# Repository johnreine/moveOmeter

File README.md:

# moveOmeter

### Privacy-Preserving IoT Monitoring for Elderly Care

> Help your loved ones live independently longer with non-invasive, radar-based health monitoring.

---

## 🎯 The Problem

Families want to care for aging loved ones while respecting their independence and privacy. Traditional monitoring requires cameras (invasive) or wearables (forgotten/rejected).

## 💡 Our Solution

**moveOmeter** uses mmWave radar technology to monitor health and activity patterns without cameras or wearables. The system tracks:

- 🚶 **Activity & Movement** - Daily patterns and mobility changes
- 😴 **Sleep Quality** - Duration, disturbances, and sleep score
- ❤️ **Vital Signs** - Heart rate and respiration (contactless)
- 🚨 **Fall Detection** - Instant alerts for falls or emergencies
- 🏠 **Presence Detection** - Know when they're home or away

**No cameras. No wearables. No user interaction required.**

---

## ✨ Key Features

### Privacy-First Design
- ✅ Radar technology (sees motion, not images)
- ✅ No video, no photos, no recording
- ✅ HIPAA-compliant architecture ready

### Real-Time Monitoring
- ✅ Live web dashboard with charts
- ✅ Mobile-responsive interface
- ✅ Instant WebSocket updates
- ✅ Historical trend analysis

### Smart & Adaptive
- ✅ Learns individual patterns
- ✅ Detects anomalies automatically
- ✅ Over-the-air firmware updates
- ✅ Remote configuration

### Secure & Scalable
- ✅ Role-based access control (admin/employee/caretaker/resident)
- ✅ End-to-end encryption
- ✅ Audit logging
- ✅ Designed to scale to millions of users

---

## 📸 Screenshots

### Real-Time Dashboard
> 🚧 *Screenshot coming soon - see [deployment guide](./deployment/QUICKSTART.md) to run locally*

**Features visible in dashboard:**
- Live timeline charts (1-hour, 12-hour, 24-hour views)
- Activity metrics (movement, presence, sleep quality)
- Device status (online/offline)
- Manual annotations
- Alert notifications

### Admin Panel
> 🚧 *Screenshot coming soon*

**Manage users and devices:**
- User management (create, edit, roles)
- Device assignment
- Access control
- Audit logs

---

## 🚀 Quick Start

### Prerequisites
- ESP32-C6 Feather development board
- DFRobot SEN0623 mmWave sensor
- Supabase account (free tier works)
- Arduino IDE 2.x

### 5-Minute Setup

1. **Clone the repository**
   ```bash
   git clone https://github.com/johnreine/moveOmeter.git
   cd moveOmeter
   ```

2. **Set up database**
   - Create Supabase project at https://supabase.com
   - Run migrations: `database/run_all_migrations.sql`

3. **Configure firmware**
   ```bash
   # Edit pictureFrame/software/mmWave_Supabase_collector/config.h
   # Add your WiFi credentials and Supabase URL/key
   ```

4. **Upload to ESP32-C6**
   - Open Arduino IDE
   - Select board: ESP32C6 Dev Module
   - Upload sketch

5. **Start dashboard**
   ```bash
   cd web/dashboard
   python3 -m http.server 8000
   open http://localhost:8000
   ```

**Full setup guide:** [deployment/QUICKSTART.md](./deployment/QUICKSTART.md)

---

## 🏗️ Architecture

```
┌──────────────────────────────────────────────────────┐
│  ESP32-C6 + mmWave Sensor (DFRobot SEN0623)         │
│  • Collects 40+ health metrics every 20 seconds     │
│  • WiFi upload to cloud                             │
│  • OTA firmware updates                             │
└─────────────────┬────────────────────────────────────┘
                  │ HTTPS Upload
                  ▼
┌──────────────────────────────────────────────────────┐
│  Supabase Backend (PostgreSQL + Auth + Realtime)    │
│  • Time-series sensor data storage                  │
│  • Role-based access control (RLS)                  │
│  • Real-time WebSocket subscriptions                │
│  • OTA firmware distribution                        │
└─────────────────┬────────────────────────────────────┘
                  │ WebSocket + REST API
                  ▼
┌──────────────────────────────────────────────────────┐
│  Web Dashboard (Vanilla JS + Chart.js)              │
│  • Live charts and metrics                          │
│  • User authentication                              │
│  • Admin panel                                      │
│  • Mobile responsive                                │
└──────────────────────────────────────────────────────┘
```

---

## 🛠️ Tech Stack

### Hardware

### Backend

### Frontend

### Firmware

### Deployment

---

## 📚 Documentation

| Document | Description |
|----------|-------------|
| **[Project Status](./PROJECT_STATUS.md)** | Complete overview of features and progress |
| **[Development Roadmap](./ROADMAP.md)** | 6-12 month development plan |
| **[AI Agent Guide](./AI_AGENT_GUIDE.md)** | For AI coding assistants (Claude, GPT, etc.) |
| **[Quick Start](./deployment/QUICKSTART.md)** | Get running in 5 minutes |
| **[Full Deployment Guide](./deployment/README.md)** | Production deployment instructions |
| **[Authentication Setup](./web/dashboard/AUTH_SETUP.md)** | User management and security |
| **[Firmware README](./pictureFrame/software/mmWave_Supabase_collector/README.md)** | ESP32-C6 firmware details |
| **[OTA Testing Guide](./database/OTA_QUICK_TEST.md)** | Test firmware updates |

---

## 🗺️ Roadmap

### ✅ Current (v1.0) - Complete
- ESP32-C6 firmware with dual collection modes
- Real-time web dashboard with charts
- Authentication system (4 user roles)
- Admin panel for user/device management
- OTA firmware update infrastructure
- Timeline annotations
- Data aggregation for performance

### 🚧 Next Month (v1.1)
- [ ] Multi-device support in dashboard
- [ ] Progressive Web App (PWA)
- [ ] Email notifications
- [ ] Activity summary reports
- [ ] Mobile-responsive design improvements

### 🔮 Next Quarter (v1.5)
- [ ] React Native mobile app (iOS + Android)
- [ ] Predictive health alerts (ML-based)
- [ ] Medication reminder integration
- [ ] Voice integration (Alexa/Google Home)
- [ ] Family sharing features

### 🎯 Long-Term Vision
- AI-powered gait analysis and fall risk prediction
- Behavior pattern recognition
- White-label solution for senior living facilities
- Integration ecosystem (Apple Health, etc.)

**Full roadmap:** [ROADMAP.md](./ROADMAP.md)

---

## 🤝 Contributing

We welcome contributions! This project is currently in active development.

### How to Contribute

1. **Read the docs**
   - [Project Status](./PROJECT_STATUS.md) - Current state
   - [Roadmap](./ROADMAP.md) - Planned features
   - [AI Agent Guide](./AI_AGENT_GUIDE.md) - Technical details

2. **Find an issue**
   - Check [Issues](https://github.com/johnreine/moveOmeter/issues) for open tasks
   - Look for `good first issue` or `help wanted` labels

3. **Fork and create a branch**
   ```bash
   git checkout -b feature/your-feature-name
   ```

4. **Make your changes**
   - Follow existing code style
   - Add tests if applicable
   - Update documentation

5. **Submit a pull request**
   - Clear description of changes
   - Reference related issues
   - Screenshots for UI changes

### Development Setup

```bash
# Clone repository
git clone https://github.com/johnreine/moveOmeter.git
cd moveOmeter

# Install Arduino libraries
# - ESPSupabase (by jhagas)
# - DFRobot_HumanDetection (by DFRobot)

# Set up Supabase
# 1. Create account at https://supabase.com
# 2. Run database/run_all_migrations.sql

# Start local dashboard
cd web/dashboard
python3 -m http.server 8000
```

### Code Style

- **JavaScript:** ES6+, async/await, template literals
- **C++:** Arduino style, comments for complex logic
- **SQL:** Uppercase keywords, clear comments
- **Documentation:** Markdown with clear headings

---

## 🌟 Use Cases

### For Families
- Monitor aging parents remotely
- Peace of mind while at work
- Early detection of health changes
- Respect privacy (no cameras)

### For Caregivers
- Track multiple clients
- Shift handoff notes
- Medication reminders
- Fall alerts

### For Senior Living Facilities
- Monitor all residents
- Staff coordination
- Compliance reporting
- Emergency response

### For Healthcare Providers
- Remote patient monitoring
- Post-discharge tracking
- Chronic condition management
- Reduce hospital readmissions

---

## 📊 Project Stats

- **40 files** of comprehensive documentation
- **16,000+ lines** of code and docs
- **40+ sensor metrics** collected
- **4 user roles** with granular permissions
- **3 timeline views** (1h, 12h, 24h)
- **97% bandwidth reduction** with smart keep-alive
- **OTA updates** for remote firmware deployment

---

## 🔐 Security & Privacy

### Privacy Protections
- ✅ No cameras or video recording
- ✅ Radar technology (motion only, not images)
- ✅ Data encrypted in transit (HTTPS)
- ✅ Data encrypted at rest (Supabase)
- ✅ Row Level Security (RLS) for data isolation

### Compliance Ready
- 🔜 HIPAA compliance architecture
- 🔜 GDPR data handling
- 🔜 SOC 2 Type II準備中

### Security Features
- Multi-factor authentication (MFA) support
- Passkey/WebAuthn ready
- Audit logging for all actions
- Role-based access control
- Automatic session management

---

## 🛡️ Testing

### Current Test Coverage
- ✅ End-to-end firmware testing
- ✅ Real-time data pipeline
- ✅ Authentication flows
- ✅ Role-based access control
- 🚧 Cross-browser compatibility
- 🚧 Scale testing (100-1000 devices)

### Tested Environments
- **Firmware:** ESP32-C6 Feather
- **Browsers:** Chrome, Firefox, Safari (desktop)
- **Database:** Supabase (PostgreSQL 15)
- **Deployment:** Ubuntu 22.04 + Nginx

---

## 💰 Cost to Run

### Development (Current)
- **Supabase:** Free tier (good for 10 devices)
- **Digital Ocean:** $10-20/month
- **Total:** ~$10-20/month

### Small Deployment (100 devices)
- **Supabase:** $25/month (Pro tier)
- **Digital Ocean:** $20/month
- **Total:** ~$45/month

### Medium Scale (1,000 devices)
- **Supabase:** $599/month (Team tier)
- **Digital Ocean/AWS:** $100-200/month
- **Total:** ~$700-800/month

**Note:** Costs scale linearly. See [ROADMAP.md](./ROADMAP.md) for scaling details.

---

## 📄 License

**Proprietary** - All rights reserved.

This project is currently not open source. Contact for licensing inquiries.

---

## 📞 Contact & Support

### Questions or Issues?
1. Check [Project Status](./PROJECT_STATUS.md) and [Roadmap](./ROADMAP.md)
2. Review [documentation](./deployment/README.md)
3. Open an [Issue](https://github.com/johnreine/moveOmeter/issues)

### Business Inquiries
- **Email:** contact@moveometer.com (TBD)
- **Website:** https://moveometer.com (TBD)

### For Contributors
- Join discussions in [Issues](https://github.com/johnreine/moveOmeter/issues)
- Submit [Pull Requests](https://github.com/johnreine/moveOmeter/pulls)
- See [AI Agent Guide](./AI_AGENT_GUIDE.md) for technical details

---

## 🙏 Acknowledgments

### Hardware
- **Adafruit** - ESP32-C6 Feather development board
- **DFRobot** - SEN0623 mmWave sensor

### Software & Services
- **Supabase** - Backend-as-a-Service platform
- **Chart.js** - Beautiful data visualization
- **Arduino** - ESP32 development framework

### Inspiration
Built with care for families supporting elderly loved ones. Inspired by the need for privacy-preserving health monitoring that maintains dignity and independence.

---

## ⭐ Star History

If you find this project useful, consider giving it a star! ⭐

---

## 📈 Project Activity

---

<div align="center">

**Made with ❤️ for better elderly care**

[Documentation](./PROJECT_STATUS.md) • [Roadmap](./ROADMAP.md) • [Contributing](#contributing) • [License](#license)

</div>

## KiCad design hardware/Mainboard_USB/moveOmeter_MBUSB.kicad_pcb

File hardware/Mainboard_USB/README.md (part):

# moveOmeter Mainboard-USB (rev A, 4 layers, routed 11/13)

A passive backboard for two SB1 rev B sensor boards. It powers both from one USB-C port and brings every sensor
signal out to headers, so a PC can run all four radars and both I2C buses through plug-in USB adapters. The mic
headers need an external I2S master (the mics are clock slaves; nothing on this board drives BCLK / WS). It has no processor. It has the same size, mounting and FFC positions the ESP32-S3 Mainboard will use, so
the enclosure and 3D-printed bracket can be tried out now. Generated 2026-10-31 from `tools/` (same generator as SB1).

## How it fits

- The board stands upright behind the SB1 V, parallel to the wall. The V stands 35 mm out, its point toward the
  room, apex at X 50. Its footprint on the front is X 20.3-79.7, y 8-84 (dashed outline on F.Fab).
- **SB1-A** (left) plugs into **J2**, **SB1-B** (right) into **J3**, each from its SB1's only ZIF, J7 (one ZIF per SB1
  since 11/8). Both are Molex 200528-0200 ZIFs (20-way, 1.0 mm, ear-tab lock), standing on end **inside the V**,
  centred on y 50.5, the same height as SB1's ZIF, **both opening toward -X**: J2's mouth at X 38.9 (turned round on
  11/8; it used to open toward the centre at X 33.0), J3's at X 67.0. **Both are wired in reverse (pad n = wire 21 - n,
  GND on pad 20)**, to match SB1's J7, so GND (wire 1) is at the bottom of both and the two links are identical.
  Cable: 20-way 1.00 mm, same-side contacts (Type A), ~51 mm, the same for both sides; never Type D. SB1-B's cable
  leaves its SB1 toward the apex, U-turns inside the V and comes into J3 from the centre; SB1-A's runs out along its SB1
  back, swings round 135 degrees and comes into J2 from the left. Full workup and drawings (pins, cable faces, X / Y
  dimensions): SB1's README, FFC link, and `docs/ffc_top_view.png`, `docs/ffc_links_flat.png`.
- The front strips where each cable runs close to the board (X 27-38.9 left of J2, X 54-67 left of J3, y 36-65) are kept
  free of parts. The bracket on H5-H8 must leave that space open too.
- **Holes:** ten M3 (3.2 mm).
  - H5-H8 at (32, 15), (68, 15), (32, 77), (68, 77), under the V (7 mm inside its top and bottom), for the bracket that holds both SB1s.
  - H1-H4 at the corners of the core (4, 4), (96, 4), (4, 86), (96, 86), and H9 / H10 at the bottom corners
    (4, 117), (96, 117), for the enclosure.
  - Keep-out 3.5 mm on both sides.

## Board (100 x 121 mm, 2 layers)

The size comes from the design: 100 mm wide for the V plus the two ZIFs. The core (y 0-90) sits behind the V; the
wing below it (y 90-121) carries the four USB-serial sticks. (150 mm until SB1 shrank by 10 mm on 10/31, 140 mm until
the sticks plugged straight in on 11/01.)

- **Front, lower left:** USB-C J1 (GCT USB4125, power only) at the left edge, mouth out. 5.1k CC pull-downs (R1, R2),
  SMBJ5.0A TVS (D1), 470 uF polymer (C1), 10 uF + 100 nF, green power LED (R3, D2).
- **Front, wing:** the bench light sensor J14, an Adafruit 4162 VEML7700 breakout (John, 10/31) in a 1x5 socket
  (Sullins PPTC051LFBN-RC), centred below the V so the SB1s don't shade it. Socket row at y 88.5; the breakout hangs
  down over the back UART headers' pin stubs (it sits ~11 mm up), sensor at about y 100. On I2C-A at 0x10, powered from
  the I2C-A adapter's 3.3 V (its own pull-ups go to that). Pins 1 VIN, 2 3Vo (not used), 3 GND, 4 SCL, 5 SDA. SB1's
  own VEML7700 footprint is DNP so the two don't clash at 0x10.
- **Back, core:**
  - I2C-A / I2C-B headers (J8, J9) at the top corners, each above a parking pad for an MCP2221A USB-I2C breakout.
    4.7k pull-up footprints to the adapter's 3.3 V (R4-R7, DNP: SB1 has its own pull-ups).
  - Mic headers (J10, J11) and status headers (J12, J13: P20, spare 1, spare 2, GND) below the MCP2221A pads at the
    sides (y 52 / 60; moved 11/4 from the middle, where their pins came through under the new ZIF positions).
- **Back, wing:** four right-angle 1x5 female sockets (J4-J7, Sullins PPTC051LGBN-RC) with the pin row at y 94. John's
  CP2102 sticks (USB-A plug, right-angle pins 3V3 / TXD / RXD / GND / +5V) plug straight in **chip side down**: resting
  on their header plastic puts their pins at the socket's height, and chip side down is the way round that lands 3V3
  on pin 1. Each stick lies flat with its USB plug hanging past the bottom edge, to plug into a hub or a USB-A extension
  lead. Its outline is on the back silk, and "CP2102 CHIP SIDE DOWN" inside it. Plugged in chip side up, its TXD would
  land on the GND pin. A 1k resistor (R8-R11)
  above each header sits in series with the adapter's TXD.
- Back silk labels read as seen from behind; pin 1 is the square pad.
- **Stackup (4 layers since 11/13):** JLC04161H-7628, 1.6 mm, as SB1 / TB1: F.Cu signals + GND pour / In1 GND plane / In2 +5V plane / B.Cu signals + GND pour. (2 layers until 11/13; four Freerouting runs never finished.)
- **Net classes (11/6):** Default 0.2 mm track, 0.175 mm clearance (as on SB1: a 0.2 mm track fits between the 1 mm-pitch ZIF pads), 0.6 / 0.3 vias; Power (+5V) 1.0 mm track, 0.2 mm clearance, 0.8 / 0.4 vias, since +5V carries both SB1s (~1.5 A peak). Neck +5V down to 0.3-0.4 mm for the last mm into the ZIF pads (pins 2-3); hole clearance 0.175 mm.
- **Checks (all pass):** courtyards, pins under the other side's parts, hole keep-outs, FFC bands free, nothing taller
  than 12 mm under the V, back parts off the MCP2221A parking pads and the stick outlines, edges (J1 is meant to be at the edge), and every
  netlist pin has its pad and net.

## Headers

| Ref | For | Pins (1 to n) |
| --- | --- | --- |
| J4 / J7 | LD6004 A / B UART (115200 default; 460800 on the bench modules since 10/14) | 3V3 (nc), TXD, RXD, GND, 5V (nc) |
| J5 / J6 | LD2450 A / B UART (256000) | 3V3 (nc), TXD, RXD, GND, 5V (nc) |
| J8 / J9 | I2C A / B | GND, 3V3, SDA, SCL |
| J14 | VEML7700 breakout (on I2C-A) | VIN, 3Vo (nc), GND, SCL, SDA |
| J10 / J11 | Mics A / B | BCLK, WS, DATA, GND |
| J12 / J13 | Status A / B | P20, spare 1, spare 2, GND |

The UART sockets take John's CP2102 sticks (Amazon B0FJRTL572, 3V3 / TXD / RXD / GND / +5V): the stick's TXD drives
the radar's RX (through the 1k) and its RXD reads the radar's TX. The sticks' 3V3 and 5V pins aren't connected, so they
don't back-feed the sensors. The stick outline (16 x 21 mm PCB) comes from sellers' listings (14-15 mm wide, 41-45 mm
with the plug, ~21 mm PCB): check it against one in hand, and check that its USB plug clears the board edge chip side
down. The MCP2221A parking pads (about 18 x 27 mm) are still placeholders until that breakout is chosen. The sockets'
3D model orientation hasn't been checked in KiCad's 3D viewer yet.

**Resetting the radars:** each adapter's TXD idles high. Without a series resistor it could hold an unpowered radar
partly up through its RX input clamp, so unplugging J1 wouldn't be a clean power-cycle. A 1k in series with each
adapter TXD (R8-R11, John 10/31) limits that current to under ~3 mA, so unplugging J1 is a reset. The 1k plus SB1's
100 ohm is far too small to matter at 256000 baud.

## Ordering

`bom_board.csv`: about $14.40 a board at qty-1 prices, including the VEML7700 breakout and its socket, not counting
the USB adapters or the FFCs.

## 3D models

KiCad's library has models for the standard parts. The rest are in `3dmodels/`, written by `tools/layout/mk3d.py` (run
by `tools/rebuild.sh`) and referenced as `${KIPRJMOD}/3dmodels/...` in the footprints. They are VRML files, so KiCad's
3D viewer shows them, but a STEP export of the board leaves them out.
- `MBUSB_Adafruit_4162_VEML7700_on_socket.wrl` (J14): Adafruit has no 3D file for the 4162 (only for the right-angle
  5378), so this one is built from their board file: outline, holes, sensor, regulator and STEMMA QT sockets. It sits
  on its header in the 1x5 socket, top at 12.6 mm.
- `Molex_200528-0200_approx.wrl` (J2, J3): a simplified housing, actuator and contacts.
- `3dmodels/vendor/Adafruit_4471_MCP2221A_Breakout.step`: Adafruit's STEP of the MCP2221A breakout, for enclosure
  CAD. It isn't a footprint on the board.
- Mounting holes and solder jumpers have no model, as in KiCad's own library.
- The Molex 200528-0200 footprint points to an official STEP file that this KiCad install doesn't have. The board uses
  the approximate model instead (`MODEL_OVERRIDE` in the board script).

## Regenerating

`sh tools/rebuild.sh` writes the schematic, library, netlist report and BOM (`tools/build.py`), the placement and
silk pads / slots / labels (`tools/layout/place_mbusb.py`), the breakout footprint (`mkfp_mbusb.py`), the board (`mkpcb_mbusb.py`), runs the rule check
(`verify_mbusb.py`) and draws `docs/MBUSB_board.png`. `tools/layout/mkpro_mbusb.py` wrote the project file once
from SB1's. Parts and nets are in `tools/design.py`.

Once you edit in KiCad, KiCad is the source of truth.

## Silkscreen labels (11/6)

`tools/layout/silkrefs.py` (run by `rebuild.sh` after the board is written) moves every reference designator beside its own part so the board can be debugged with everything fitted: never under a part body, off pads, other silk and other labels, 0.5 mm inside the edge. Text is 0.8 mm (0.12 stroke), dropping to 0.7 / 0.6 mm only where there's no room (on SB1 only C11, at 0.6 mm). The module pin labels under the LD6004 / LD2450 and the CP2102 notes stay where their footprints put them. If you move a part in KiCad, move its label by hand: once routing starts, KiCad owns the board.

## Mounting holes: screw keep-outs (11/6)

All ten M3 holes are unplated. Rule areas ban tracks and vias within 3.45 mm of each hole centre on both sides (bracket
screw heads on the front at H5-H8, feet / nuts on the back); GND pour is allowed there.

## Routing prep (11/13)

`tools/layout/fanout_mbusb.py` (run by `rebuild.sh` right after the board is written) applies SB1's routing lessons:
- **Edge strips:** a 0.4 mm no-track / no-via rule area inside each edge on both layers. Freerouting ignores KiCad's
  0.5 mm copper-to-edge rule; the strips put it in the DSN. Pads and pour are allowed there.
- **GND fan-out:** 18 locked GND vias, one per SMD GND pad, each on a 0.3 mm stub: the ZIF GND pads (6, 9, 11, 14, 17,
  20) on the housing side at x 41.3 (J2) / 69.43 (J3), and C2, C3, D1, D2, R1, R2. They keep the two pours joined
  however the tracks cut them up.
- **+5V into the ZIFs:** pads 18 and 19 joined at 0.4 mm, out 0.4 mm past the courtyard, then 1.0 mm for 1.1 mm, so
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
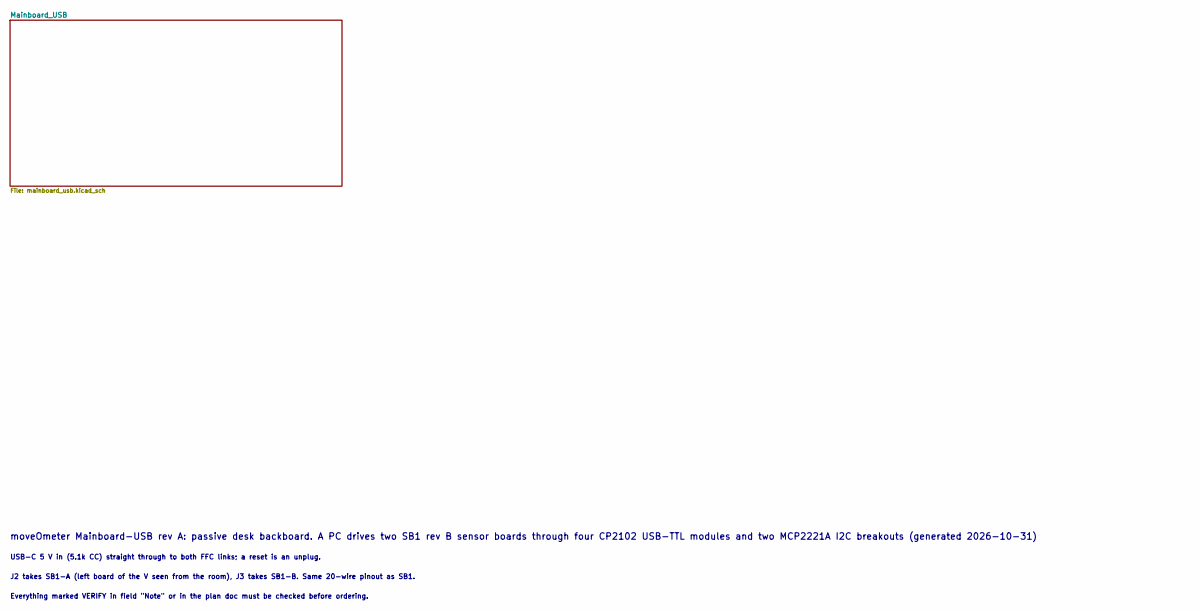
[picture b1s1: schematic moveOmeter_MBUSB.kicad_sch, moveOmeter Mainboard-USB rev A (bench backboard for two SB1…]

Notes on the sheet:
moveOmeter Mainboard-USB rev A: passive desk backboard. A PC drives two SB1 rev B sensor boards through four CP2102 USB-TTL modules and two MCP2221A I2C breakouts (generated 2026-10-31)
USB-C 5 V in (5.1k CC) straight through to both FFC links; a reset is an unplug.
J2 takes SB1-A (left board of the V seen from the room), J3 takes SB1-B. Same 20-wire pinout as SB1.
Everything marked VERIFY in field "Note" or in the plan doc must be checked before ordering.

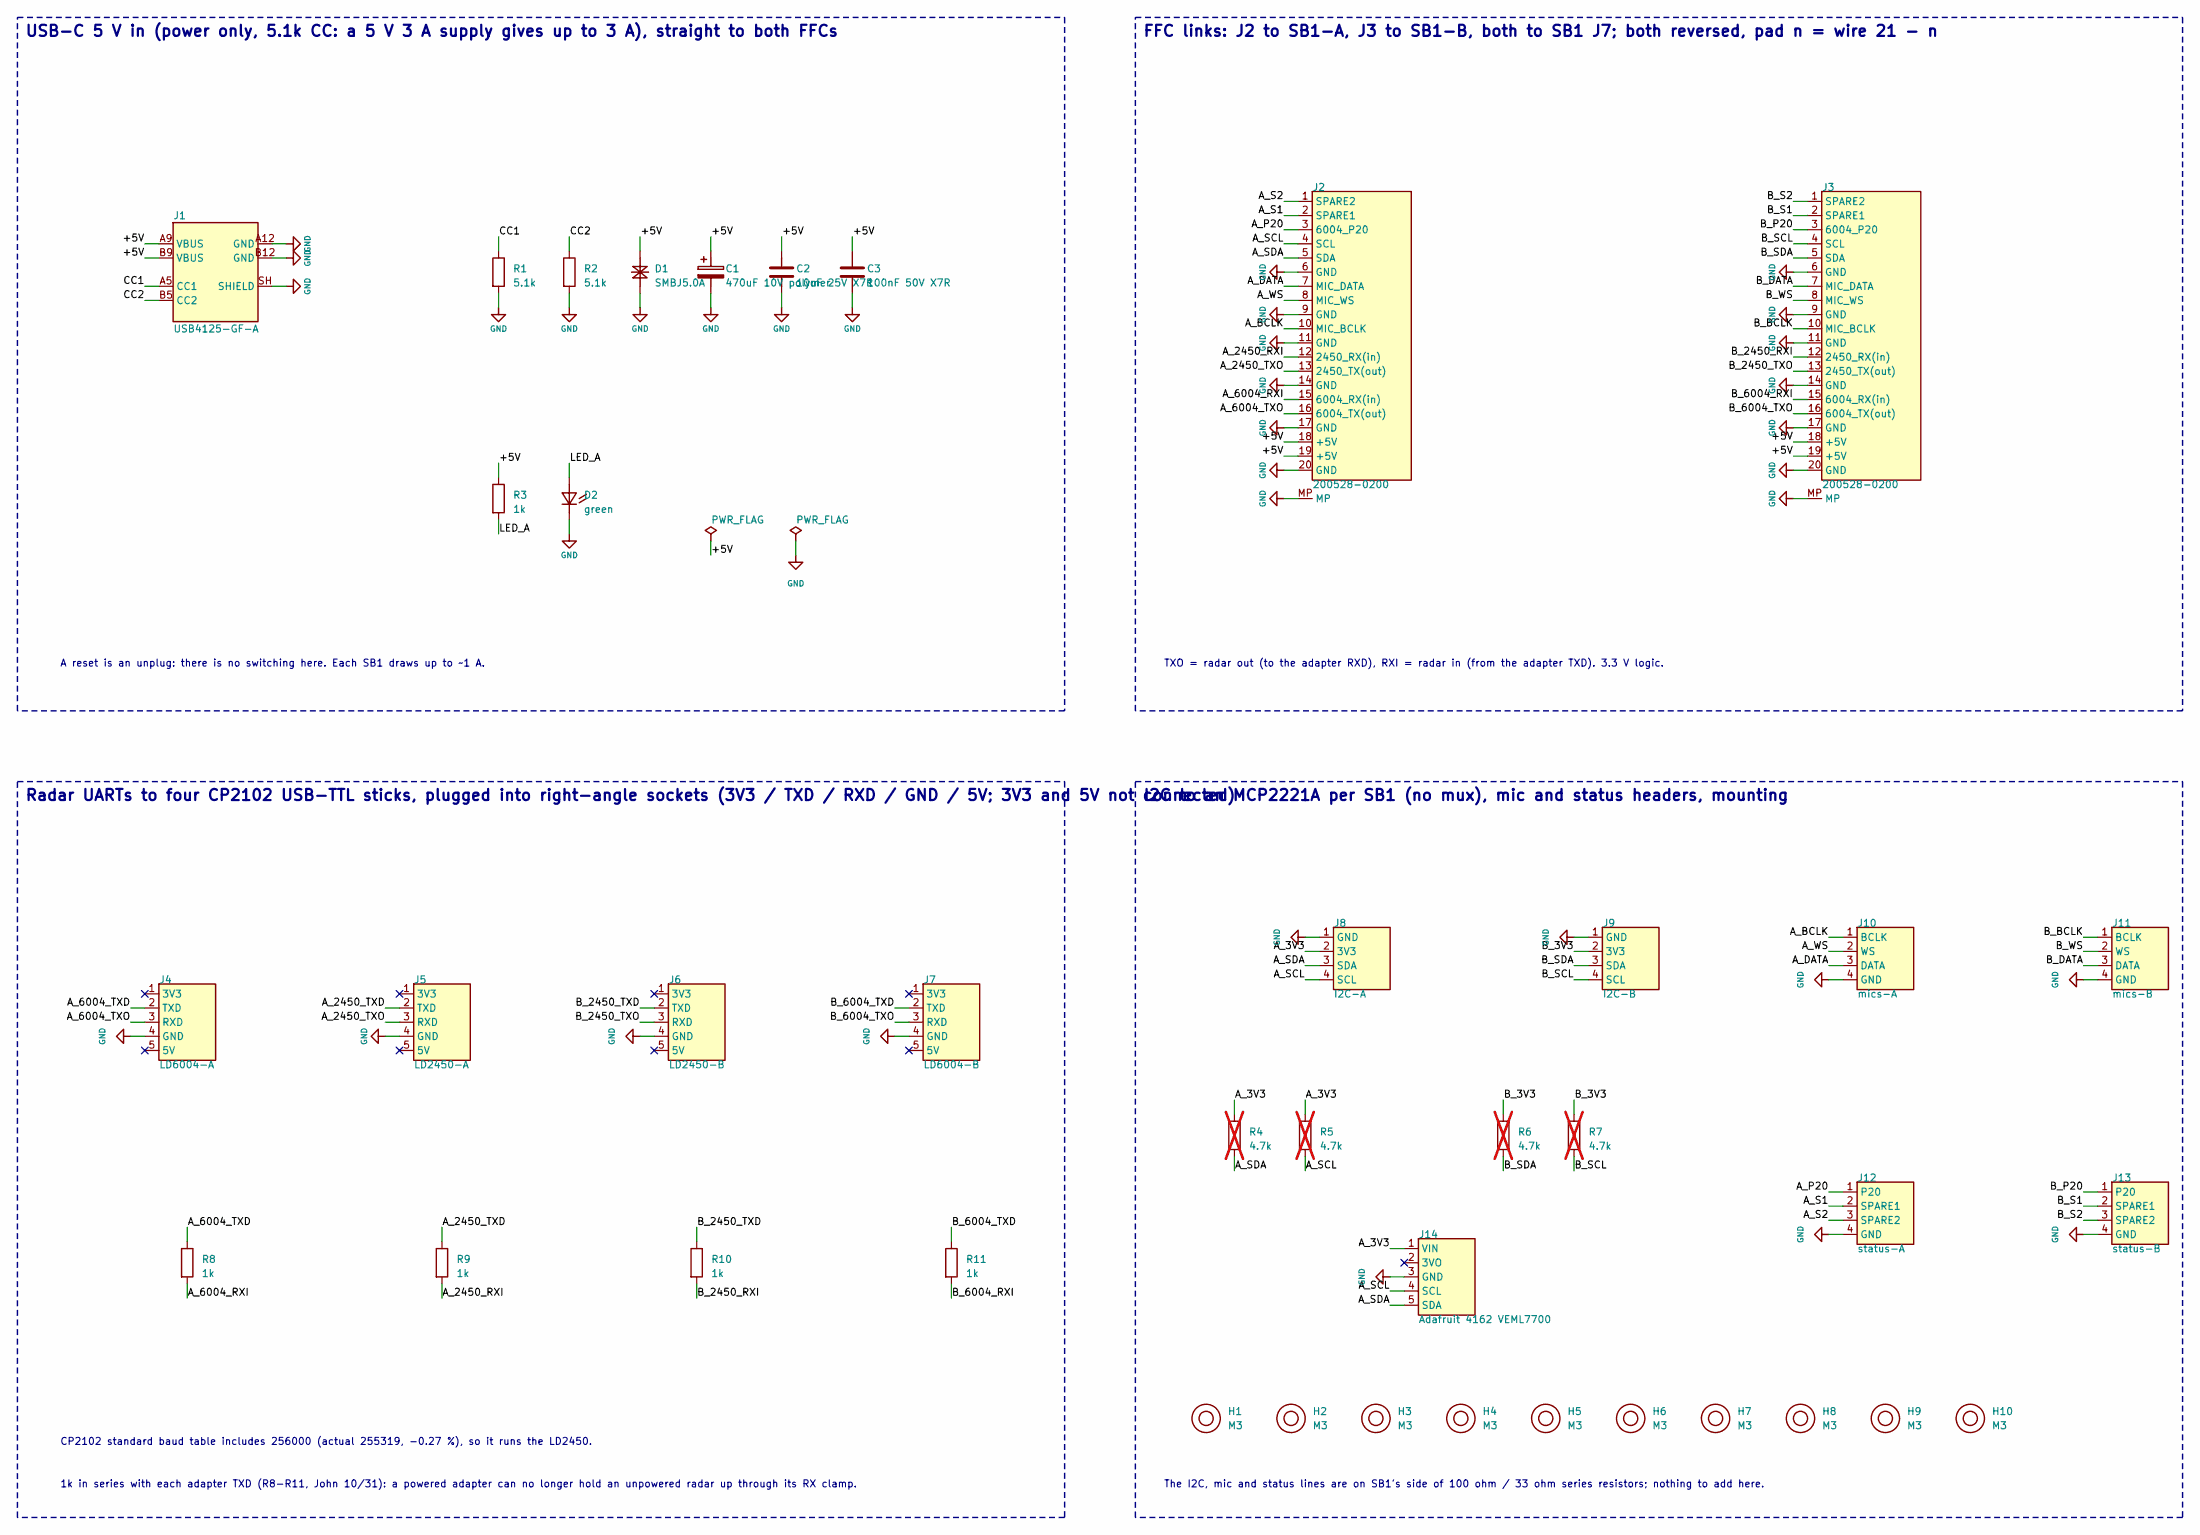
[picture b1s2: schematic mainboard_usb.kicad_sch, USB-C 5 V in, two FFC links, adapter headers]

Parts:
C1: 470uF 10V polymer; CP_Radial_D8.0mm_P3.50mm; MPN A759KS477M1AAAE014
C2: 10uF 25V X7R; C_1210_3225Metric_Pad1.33x2.70mm_HandSolder; MPN GRM32DR71E106KA12L
C3: 100nF 50V X7R; C_1206_3216Metric_Pad1.33x1.80mm_HandSolder; MPN CL31B104KBCNNNC
D1: SMBJ5.0A; D_SMB_Handsoldering; MPN SMBJ5.0A
D2: green; LED_1206_3216Metric_Pad1.42x1.75mm_HandSolder; MPN LTST-C150GKT
H1, H2, H3, H4, H5, H6, H7, H8, H9, H10: M3; MountingHole_3.2mm_M3
J1: USB4125-GF-A; USB_C_Receptacle_GCT_USB4125-xx-x_6P_TopMnt_Horizontal; MPN USB4125-GF-A
J2, J3: 200528-0200; Molex_200528-0200_1x20-1MP_P1.00mm_Horizontal; MPN 200528-0200
J4: LD6004-A; CP2102_Stick_Socket_1x05_P2.54mm_Horizontal; MPN PPTC051LGBN-RC
J5: LD2450-A; CP2102_Stick_Socket_1x05_P2.54mm_Horizontal; MPN PPTC051LGBN-RC
J6: LD2450-B; CP2102_Stick_Socket_1x05_P2.54mm_Horizontal; MPN PPTC051LGBN-RC
J7: LD6004-B; CP2102_Stick_Socket_1x05_P2.54mm_Horizontal; MPN PPTC051LGBN-RC
J8: I2C-A; PinHeader_1x04_P2.54mm_Vertical; MPN PEC04SAAN
J9: I2C-B; PinHeader_1x04_P2.54mm_Vertical; MPN PEC04SAAN
J10: mics-A; PinHeader_1x04_P2.54mm_Vertical; MPN PEC04SAAN
J11: mics-B; PinHeader_1x04_P2.54mm_Vertical; MPN PEC04SAAN
J12: status-A; PinHeader_1x04_P2.54mm_Vertical; MPN PEC04SAAN
J13: status-B; PinHeader_1x04_P2.54mm_Vertical; MPN PEC04SAAN
J14: Adafruit 4162 VEML7700; Adafruit_VEML7700_Breakout_Socket_1x05; MPN PPTC051LFBN-RC
R1, R2: 5.1k; R_1206_3216Metric_Pad1.30x1.75mm_HandSolder; MPN RC1206FR-075K1L
R3, R8, R9, R10, R11: 1k; R_1206_3216Metric_Pad1.30x1.75mm_HandSolder; MPN RC1206FR-071KL
R4, R5, R6, R7: 4.7k; R_1206_3216Metric_Pad1.30x1.75mm_HandSolder; MPN RC1206FR-074K7L; not fitted

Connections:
/Mainboard_USB/+5V: C1.1 (+), C2.1, C3.1, D1.1 (K), J1.A9 (VBUS), J1.B9 (VBUS), J2.18 (+5V), J2.19 (+5V), J3.18 (+5V), J3.19 (+5V), R3.1
/Mainboard_USB/A_3V3: J8.2 (3V3), J14.1 (VIN), R4.1, R5.1
/Mainboard_USB/A_2450_RXI: J2.12 (2450_RX(in)), R9.2
/Mainboard_USB/A_2450_TXD: J5.2 (TXD), R9.1
/Mainboard_USB/A_2450_TXO: J2.13 (2450_TX(out)), J5.3 (RXD)
/Mainboard_USB/A_6004_RXI: J2.15 (6004_RX(in)), R8.2
/Mainboard_USB/A_6004_TXD: J4.2 (TXD), R8.1
/Mainboard_USB/A_6004_TXO: J2.16 (6004_TX(out)), J4.3 (RXD)
/Mainboard_USB/A_BCLK: J2.10 (MIC_BCLK), J10.1 (BCLK)
/Mainboard_USB/A_DATA: J2.7 (MIC_DATA), J10.3 (DATA)
/Mainboard_USB/A_P20: J2.3 (6004_P20), J12.1 (P20)
/Mainboard_USB/A_S1: J2.2 (SPARE1), J12.2 (SPARE1)
/Mainboard_USB/A_S2: J2.1 (SPARE2), J12.3 (SPARE2)
/Mainboard_USB/A_SCL: J2.4 (SCL), J8.4 (SCL), J14.4 (SCL), R5.2
/Mainboard_USB/A_SDA: J2.5 (SDA), J8.3 (SDA), J14.5 (SDA), R4.2
/Mainboard_USB/A_WS: J2.8 (MIC_WS), J10.2 (WS)
/Mainboard_USB/B_3V3: J9.2 (3V3), R6.1, R7.1
/Mainboard_USB/B_2450_RXI: J3.12 (2450_RX(in)), R10.2
/Mainboard_USB/B_2450_TXD: J6.2 (TXD), R10.1
/Mainboard_USB/B_2450_TXO: J3.13 (2450_TX(out)), J6.3 (RXD)
/Mainboard_USB/B_6004_RXI: J3.15 (6004_RX(in)), R11.2
/Mainboard_USB/B_6004_TXD: J7.2 (TXD), R11.1
/Mainboard_USB/B_6004_TXO: J3.16 (6004_TX(out)), J7.3 (RXD)
/Mainboard_USB/B_BCLK: J3.10 (MIC_BCLK), J11.1 (BCLK)
/Mainboard_USB/B_DATA: J3.7 (MIC_DATA), J11.3 (DATA)
/Mainboard_USB/B_P20: J3.3 (6004_P20), J13.1 (P20)
/Mainboard_USB/B_S1: J3.2 (SPARE1), J13.2 (SPARE1)
/Mainboard_USB/B_S2: J3.1 (SPARE2), J13.3 (SPARE2)
/Mainboard_USB/B_SCL: J3.4 (SCL), J9.4 (SCL), R7.2
/Mainboard_USB/B_SDA: J3.5 (SDA), J9.3 (SDA), R6.2
/Mainboard_USB/B_WS: J3.8 (MIC_WS), J11.2 (WS)
/Mainboard_USB/CC1: J1.A5 (CC1), R1.1
/Mainboard_USB/CC2: J1.B5 (CC2), R2.1
/Mainboard_USB/LED_A: D2.2 (A), R3.2
GND: C1.2 (-), C2.2, C3.2, D1.2 (A), D2.1 (K), J1.A12 (GND), J1.B12 (GND), J1.SH (SHIELD), J2.6 (GND), J2.9 (GND), J2.11 (GND), J2.14 (GND), J2.17 (GND), J2.20 (GND), J2.MP, J3.6 (GND), J3.9 (GND), J3.11 (GND), J3.14 (GND), J3.17 (GND), J3.20 (GND), J3.MP, J4.4 (GND), J5.4 (GND), J6.4 (GND), J7.4 (GND), J8.1 (GND), J9.1 (GND), J10.4 (GND), J11.4 (GND), J12.4 (GND), J13.4 (GND), J14.3 (GND), R1.2, R2.2

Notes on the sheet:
USB-C 5 V in (power only, 5.1k CC: a 5 V 3 A supply gives up to 3 A), straight to both FFCs
A reset is an unplug: there is no switching here. Each SB1 draws up to ~1 A.
FFC links: J2 to SB1-A, J3 to SB1-B, both to SB1 J7; both reversed, pad n = wire 21 - n
TXO = radar out (to the adapter RXD), RXI = radar in (from the adapter TXD). 3.3 V logic.
Radar UARTs to four CP2102 USB-TTL sticks, plugged into right-angle sockets (3V3 / TXD / RXD / GND / 5V; 3V3 and 5V not connected)
1k in series with each adapter TXD (R8-R11, John 10/31): a powered adapter can no longer hold an unpowered radar up through its RX clamp.
CP2102 standard baud table includes 256000 (actual 255319, -0.27 %), so it runs the LD2450.
I2C to an MCP2221A per SB1 (no mux), mic and status headers, mounting
The I2C, mic and status lines are on SB1's side of 100 ohm / 33 ohm series resistors; nothing to add here.

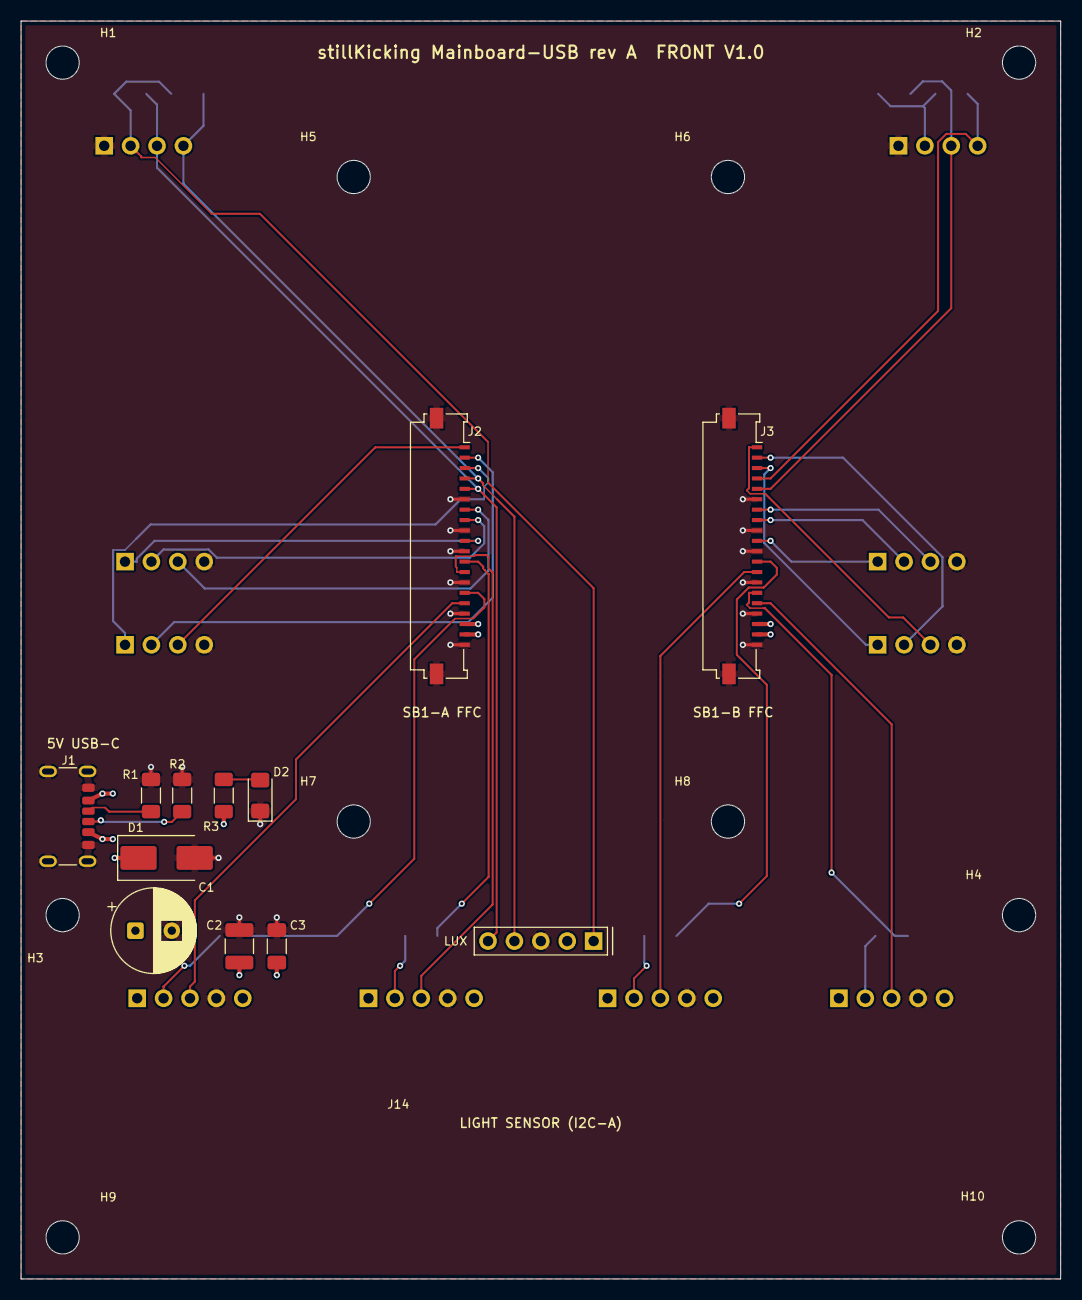
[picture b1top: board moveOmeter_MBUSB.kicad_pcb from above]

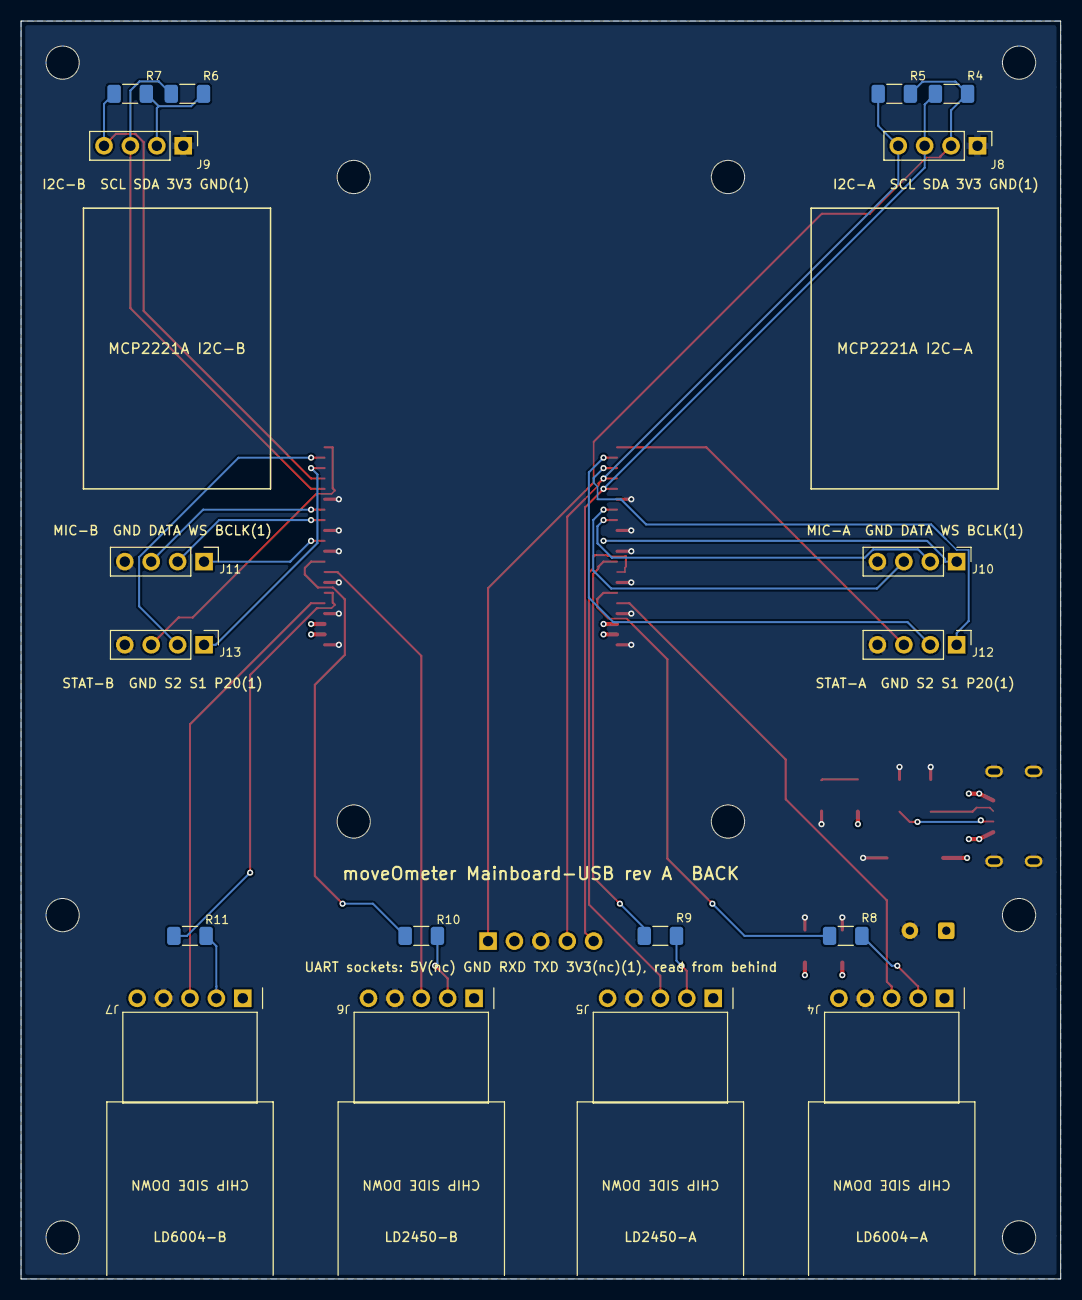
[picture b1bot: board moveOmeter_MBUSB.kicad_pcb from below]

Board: 4 copper layers, 100.0 x 121.0 mm, 40 parts (18 on the bottom side), 35 nets.

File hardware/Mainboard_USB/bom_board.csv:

Refs,Qty per board,Value,Manufacturer,MPN,Footprint,Fit,Vendor Part #,"Price (qty 1, USD)",Ext price per board (USD),Vendor Link,Datasheet
C1,1,470uF 10V polymer,KEMET,A759KS477M1AAAE014,CP_Radial_D8.0mm_P3.50mm,,399-A759KS477M1AAAE014-ND,0.82,0.82,https://www.digikey.com/en/products/result?keywords=399-A759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,https://www.mouser.com/datasheet/2/447/KEM_A4072_A759-3316694.pdf
C2,1,10uF 25V X7R,Murata,GRM32DR71E106KA12L,C_1210_3225Metric_Pad1.33x2.70mm_HandSolder,,490-1867-1-ND,0.93,0.93,https://www.digikey.com/en/products/detail/murata-electronic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,https://pim.murata.com/asset/pim4/ceramicCapacitorSMD/GRM32D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
C3,1,100nF 50V X7R,Samsung,CL31B104KBCNNNC,C_1206_3216Metric_Pad1.33x1.80mm_HandSolder,,1276-1017-1-ND,0.15,0.15,https://www.digikey.com/en/products/detail/samsung-electro-m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,https://weblib.samsungsem.com/mlcc/mlcc-ec-data-sheet.do?par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
D1,1,SMBJ5.0A,Littelfuse,SMBJ5.0A,D_SMB_Handsoldering,,SMBJ5.0ALFCT-ND,0.50,0.5,https://www.digikey.com/en/products/detail/littelfuse-inc/SM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,https://www.littelfuse.com/assetdocs/tvs-diodes-smbj-series-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
D2,1,green,Lite-On,LTST-C150GKT,LED_1206_3216Metric_Pad1.42x1.75mm_HandSolder,,160-1169-1-ND,0.21,0.21,https://www.digikey.com/en/products/detail/liteon/LTST-C150G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,https://www.mouser.com/datasheet/2/239/Lite_On_LTST_C150GKT-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
J1,1,USB4125-GF-A,GCT,USB4125-GF-A,USB_C_Receptacle_GCT_USB4125-xx-x_6P_TopMnt_Horizontal,,2073-USB4125-GF-ACT-ND,0.65,0.65,https://www.digikey.com/en/products/detail/gct-emea-ltd/USB4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,https://gct.co/files/drawings/usb4125.pdf
"J2, J3",2,200528-0200,Molex,200528-0200,Molex_200528-0200_1x20-1MP_P1.00mm_Horizontal,,900-2005280200CT-ND,0.89,1.78,https://www.digikey.com/en/products/detail/molex/2005280200/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,https://www.molex.com/en-us/products/part-detail/2005280200
J4,1,LD6004-A,Sullins,PPTC051LGBN-RC,CP2102_Stick_Socket_1x05_P2.54mm_Horizontal,,S5441-ND,0.63,0.63,https://www.digikey.com/en/products/detail/sullins-connector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,https://www.digikey.com/en/products/detail/sullins-connector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
J5,1,LD2450-A,Sullins,PPTC051LGBN-RC,CP2102_Stick_Socket_1x05_P2.54mm_Horizontal,,S5441-ND,0.63,0.63,https://www.digikey.com/en/products/detail/sullins-connector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,https://www.digikey.com/en/products/detail/sullins-connector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
J6,1,LD2450-B,Sullins,PPTC051LGBN-RC,CP2102_Stick_Socket_1x05_P2.54mm_Horizontal,,S5441-ND,0.63,0.63,https://www.digikey.com/en/products/detail/sullins-connector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,https://www.digikey.com/en/products/detail/sullins-connector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
J7,1,LD6004-B,Sullins,PPTC051LGBN-RC,CP2102_Stick_Socket_1x05_P2.54mm_Horizontal,,S5441-ND,0.63,0.63,https://www.digikey.com/en/products/detail/sullins-connector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,https://www.digikey.com/en/products/detail/sullins-connector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
J8,1,I2C-A,Sullins,PEC04SAAN,PinHeader_1x04_P2.54mm_Vertical,,35-PEC04SAAN-ND,0.30,0.3,https://www.digikey.com/en/products/detail/sullins-connector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,https://www.sullinscorp.com/catalogs/77_PAGE108-109_.100_MAL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
J9,1,I2C-B,Sullins,PEC04SAAN,PinHeader_1x04_P2.54mm_Vertical,,35-PEC04SAAN-ND,0.30,0.3,https://www.digikey.com/en/products/detail/sullins-connector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,https://www.sullinscorp.com/catalogs/77_PAGE108-109_.100_MAL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
J10,1,mics-A,Sullins,PEC04SAAN,PinHeader_1x04_P2.54mm_Vertical,,35-PEC04SAAN-ND,0.30,0.3,https://www.digikey.com/en/products/detail/sullins-connector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,https://www.sullinscorp.com/catalogs/77_PAGE108-109_.100_MAL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
J11,1,mics-B,Sullins,PEC04SAAN,PinHeader_1x04_P2.54mm_Vertical,,35-PEC04SAAN-ND,0.30,0.3,https://www.digikey.com/en/products/detail/sullins-connector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,https://www.sullinscorp.com/catalogs/77_PAGE108-109_.100_MAL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
J12,1,status-A,Sullins,PEC04SAAN,PinHeader_1x04_P2.54mm_Vertical,,35-PEC04SAAN-ND,0.30,0.3,https://www.digikey.com/en/products/detail/sullins-connector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,https://www.sullinscorp.com/catalogs/77_PAGE108-109_.100_MAL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
J13,1,status-B,Sullins,PEC04SAAN,PinHeader_1x04_P2.54mm_Vertical,,35-PEC04SAAN-ND,0.30,0.3,https://www.digikey.com/en/products/detail/sullins-connector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,https://www.sullinscorp.com/catalogs/77_PAGE108-109_.100_MAL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
J14,1,Adafruit 4162 VEML7700,Sullins,PPTC051LFBN-RC,Adafruit_VEML7700_Breakout_Socket_1x05,,S6103-ND,0.44,0.44,https://www.digikey.com/en/products/detail/sullins-connector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,"https://www.sullinscorp.com/drawings/78_P(N)PxCxxxLFBN-RC,_10492-H.pdf"
"R1, R2",2,5.1k,Yageo,RC1206FR-075K1L,R_1206_3216Metric_Pad1.30x1.75mm_HandSolder,,311-5.10KFRCT-ND,0.11,0.22,https://www.digikey.com/en/products/detail/yageo/RC1206FR-07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,https://yageogroup.com/content/datasheet/asset/file/PYU-RC_G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
"R3, R8, R9, R10, R11",5,1k,Yageo,RC1206FR-071KL,R_1206_3216Metric_Pad1.30x1.75mm_HandSolder,,311-1.00KFRCT-ND,0.10,0.5,https://www.digikey.com/en/products/detail/yageo/RC1206FR-07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,https://yageogroup.com/content/datasheet/asset/file/PYU-RC_G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
"R4, R5, R6, R7",4,4.7k,Yageo,RC1206FR-074K7L,R_1206_3216Metric_Pad1.30x1.75mm_HandSolder,DNP,311-4.70KFRCT-ND,0.10,,https://www.digikey.com/en/products/detail/yageo/RC1206FR-07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,https://yageogroup.com/content/datasheet/asset/file/PYU-RC_G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
(with J14),1,VEML7700 lux sensor breakout,Adafruit,Adafruit 4162,,,Adafruit 4162,4.95,4.95,https://www.adafruit.com/product/4162,https://learn.adafruit.com/adafruit-veml7700

"Total per board at qty-1 prices (fitted parts, sockets and shunts included)",,,,,,,,,15.47,,
"Prices: DigiKey qty-1 unit prices in USD from DigiKey's feed via Octopart/TrustedParts, checked 2026-10-17 (1206/1210 passives and SB1 parts 2026-10-25; SB1 rev B and Mainboard-USB parts 2026-10-31); recheck before ordering",,,,,,,,,,,

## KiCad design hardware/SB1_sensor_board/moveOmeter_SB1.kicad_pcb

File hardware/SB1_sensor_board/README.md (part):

# moveOmeter sensor board SB1 (rev B, routed 11/10; final checks 11/13)

Rev B is the minimal, hand-solderable sensor assembly used unchanged in the nightlight and the frame. One HLK-LD6004
(60 GHz), one HLK-LD2450 (24 GHz), two I2S mic breakouts, a VEML7700 light sensor and an ID EEPROM on a 42 x 76 mm,
4-layer board. Power switching, current monitoring and USB-serial moved to the backboard (Mainboard-USB now, the
ESP32-S3 Mainboard later). Generated 2026-10-31 from `tools/`.

Rev A (70 x 56.5 mm, USB-C + CH340C per sensor, muxes, INA219s, 2x10 ribbon) is kept in `docs/revA/`, with its
README, schematics, board and the tools that built it.

**Product arrangement:** two identical SB1s per unit, fronts 90 degrees apart in a V with the point toward the room.
The V stands 35 mm out from the backboard, which stands upright behind it, parallel to the wall, so the unit stays
slim. Each SB1 connects with a short 20-way 1.0 mm FFC from the ZIF at its outer end to a ZIF on the backboard.

## Open it

Open `moveOmeter_SB1.kicad_pro` in KiCad 10. The schematics are KiCad 8 format until KiCad saves them. Project
libraries: `lib/SB1.kicad_sym` and `lib/SB1.pretty`. Run ERC, then Update PCB from Schematic (F8): it should only
refresh fields. Run DRC before routing.

## Sheets

| Sheet | File | Contents |
| --- | --- | --- |
| Power_IO | power_io.kicad_sch | FFC ZIF J7 (one since 11/8), 5 V TVS, LP5907 3.3 V LDO, LED, two I2S mics, 24AA256UID, VEML7700, I2C pull-ups, spare header |
| LD6004 | ld6004.kicad_sch | Isolation link, TLV62569 3.3 V buck, UART series resistors, board-mounted module |
| LD2450 | ld2450.kicad_sch | Isolation link, ferrite + bulk filtering on 5 V, UART series resistors, module mounted upright |

## How it works

- **Power:** 5 V comes in on two FFC wires, with an SMBJ5.0A TVS and 10 uF + 100 nF at the connectors.
  - The LD6004 gets 3.3 V from a TLV62569 buck (453k / 100k divider, 3.32 V).
  - The LD2450 runs from 5 V through a ferrite and 22 uF + 10 uF + 100 nF.
  - An LP5907 makes +3V3 for the mics, EEPROM, light sensor and I2C pull-ups only (~5 mA). It never feeds a radar.
- **Isolation links:** each radar's 5 V goes through a fitted 0 ohm 1206 (R7 LD6004, R12 LD2450), with an open
  solder jumper beside it (JP1, JP2). Remove the resistor to run the other radar alone; bridge the jumper to put it
  back without a resistor.
- **Serial:** 100 ohm series resistors on every UART line: the radar-TX one at the module, the radar-RX one at the
  ZIFs. LD6004 P20 goes straight to the FFC. UART logic is 3.3 V. Baud rates: LD2450 256000; LD6004 115200 by datasheet default, but the bench modules were set to 460800 on 10/14 and keep that setting, so run the host at whatever the module is set to.
- **Mics:** two Adafruit 6049 I2S breakouts, soldered flat to the back at the top edge (see Layout). J1 has SEL
  low (left channel), J2 SEL high (right), so they share one data line. 33 ohm series resistors: BCLK and WS at the
  ZIFs, data at the mics.
- **I2C:** 24AA256UID ID EEPROM at 0x50 (unique 32-bit serial) and VEML7700 at 0x10, with 4.7k pull-ups to +3V3. Both
  SB1s are identical; the backboard keeps them on separate buses.
- **Light sensor:** the VEML7700-TT footprint (U4 + C8) stays on the front, but both are DNP for now (John, 10/31): on
  the bench the light sensor is an Adafruit 4162 breakout on Mainboard-USB, at the same address (0x10). Fit U4 and C8
  (hot air) when the board goes into a unit without that breakout.
- **LED:** red 5 V LED, off unless JP3 is bridged.
- **Spare:** J6 (1x3) brings out the two spare FFC wires and GND.

## FFC link (J7, Molex 200528-0200)

20-way, 1.0 mm pitch ZIF, bottom contact, front-flip actuator (KiCad's footprint calls it "BackFlip"; Molex lists the
200528 as front flip), with an ear-tab lock that holds an eared cable in through shipping. **Since 11/8 (John) there is
one ZIF per board, J7 (left edge, seen from the front), standing on end on the back and opening toward the board's
centre.** J3 (the right-edge twin, wired in parallel) is gone, so each signal has one connector and no stub, and there
is no bus across the board. J7 is wired in reverse (pad n = wire 21 - n, since 11/7), so GND is at the bottom.
Pin numbers below are FFC wires.

| Pin | Signal | Pin | Signal |
| --- | --- | --- | --- |
| 1 | GND | 11 | I2S BCLK |
| 2 | +5 V in | 12 | GND |
| 3 | +5 V in | 13 | I2S WS |
| 4 | GND | 14 | I2S data (mics to backboard) |
| 5 | LD6004 TX (sensor to backboard) | 15 | GND |
| 6 | LD6004 RX (backboard to sensor) | 16 | I2C SDA |
| 7 | GND | 17 | I2C SCL |
| 8 | LD2450 TX (sensor to backboard) | 18 | LD6004 P20 |
| 9 | LD2450 RX (backboard to sensor) | 19 | Spare 1 |
| 10 | GND | 20 | Spare 2 |

Drawings: `docs/ffc_top_view.png` (top view to scale with X / Y dimensions, cable paths, contact face; script
`tools/layout/ffc_single_draw.py`) and `docs/ffc_links_flat.png` (each link unfolded, pin heights at both ends;
`tools/layout/ffc_draw.py`).

### Cable routes (loop routing 11/4; one ZIF 11/8)

Top view, mm: X from Mainboard-USB's left edge seen from the room, Y out from its front face. SB1-A's back runs from its
outer end (20.3, 5.3) to the apex (50, 35); SB1-B mirrors it. Both SB1s use J7, so on SB1-B it is at the outer end and on
SB1-A it is near the apex.

- **SB1-B (right):** the cable leaves J7 at (72.8, 9.6) toward the apex, lies flat on the back for about 11 mm, makes a
  U-turn (r 6 mm) into the V (nearest the room at (60.6, 19.4)), runs back toward the wall and bends 45 degrees (r 6 mm)
  into Mainboard-USB J3, mouth (67.0, 1.0), coming in from the centre. Unchanged from 11/4.
- **SB1-A (left):** J7 sits near the apex, its mouth at board x 7.9 opening toward SB1-A's outer end. The cable lies flat
  on the back for about 24 mm (board x 7.9 to ~31.9, over the LD2450 ground area, where no parts are allowed), then
  swings round 135 degrees (r 6 mm; furthest out at (27.0, 7.0), 2.8 mm clear of the SB1-A back) and comes straight into
  Mainboard-USB J2, mouth (38.9, 1.0), from the left. J2 was turned round on 11/8 to open toward -X.
- The two cables stay 15 mm apart. Every bend is across the cable's thickness, about a vertical axis, and the cable
  never twists, so each conductor stays at the same height from end to end.
- Both need 44 mm free plus about 3.5 mm inside each connector: **the same ~51 mm cable on both sides.** Length error
  goes into the U-turn (SB1-B) or the swing (SB1-A).
- On SB1 the cable needs a flat lane on the back: from J7's mouth to the LD2450 ground zone (x 7.9-10.5) and, for
  SB1-A's longer run, from the zone to x 34.1 (where J3 used to be), y 29.4-55.6, full cable width including ear tabs.
  `place_sb1b.py` keeps both clear (`LANES` in `docs/layout.json`) and `verify_sb1b.py` fails if a part lands in them.
- **Assembly:** SB1-A's ZIF is in the narrow part of the V (about 9 mm between the board backs there). Plug its cable in
  and close the latch before both boards go into the bracket.

### Pins and cable faces (11/8; from the pad positions in both board files)

| Connector | Wired | GND (wire 1) at | Pad at the bottom |
| --- | --- | --- | --- |
| SB1 J7 (both boards) | **reversed, pad n = wire 21 - n** | bottom (SB1 y 52 = MB y 60) | pad 20 |
| Mainboard-USB J2 (SB1-A) | **reversed** (turned round 11/8) | bottom (MB y 60) | pad 20 |
| Mainboard-USB J3 (SB1-B) | **reversed** | bottom (MB y 60) | pad 20 |

- Both links are now identical: SB1 J7 to a reversed Mainboard ZIF that opens toward -X. The check script matches every
  SB1 J7 pad with the Mainboard-USB pad at the same height: 20 / 20 signals agree on both links. The full Mainboard
  must do the same (both ZIFs reversed, both opening toward -X, J2 at X 38.9).
- **Contact face:** both connectors are bottom contact, so the exposed conductors face the SB1 at one end and the
  Mainboard at the other. Following each cable round (SB1-B: U-turn then 45 degrees; SB1-A: one 135 degree swing), that
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
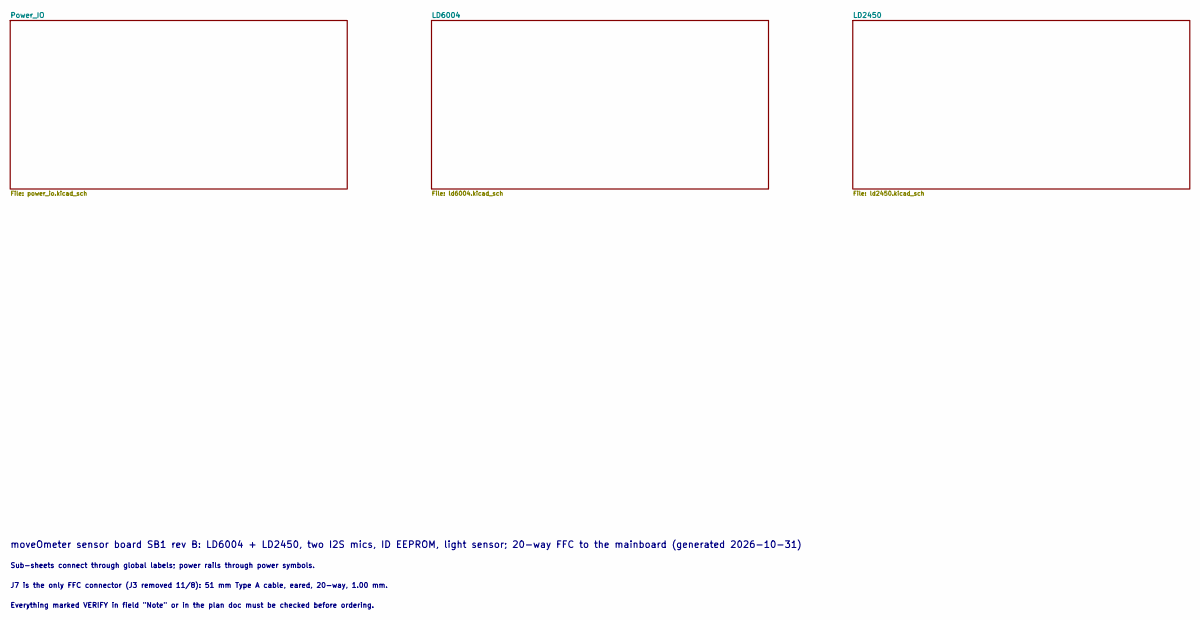
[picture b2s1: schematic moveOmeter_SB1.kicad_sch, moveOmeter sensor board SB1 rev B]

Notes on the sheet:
Everything marked VERIFY in field "Note" or in the plan doc must be checked before ordering.
J7 is the only FFC connector (J3 removed 11/8): 51 mm Type A cable, eared, 20-way, 1.00 mm.
Sub-sheets connect through global labels; power rails through power symbols.
moveOmeter sensor board SB1 rev B: LD6004 + LD2450, two I2S mics, ID EEPROM, light sensor; 20-way FFC to the mainboard (generated 2026-10-31)
